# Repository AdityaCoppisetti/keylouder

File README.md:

hey im dhruv coppisetti and i love mechanical keyboards!
mainly 60 percents to be honest. 

with hackclub's macondo program where they fund you for the project that you make,
i decided that i should give this project a try and for the longest time i left it
abandoned because i couldn't figure out the keyboard layout, but then i watched a ton of
youtube tutorials and i got the hang of it. 

how is my keyboard different than other 60 percent keyboards?

well for starters its made completely by me including the pcb and the case and everything down to the tiniest bit

and then i did this really unique thing all because i had a tiny bit of space beneath the main controller of the keyboard (raspberry pi pico)
so i thought i should add a led matrix.

i was loooking at a tutorial where they had made their own led matrix module and it got me thinking what if i made my own
hotswappable modules

and so i did just that 

i made the keyboards pcb firstly and here is how that looks like 

but the wiring and the annotation was all wrong so i made it again plus i had totally forgotton to add stabilizers

so i made the schematic again and made a new pcb 

i landed with this pcb 

and the extra space beneath the pi pico gave me the idea and the space to add swappable modules 

and so i made a led matrix pcb and here is how that looks like 

the routing for this pcb took me A WHILLLEEE but i had  tons of fun doing it 
its really fun to take such tasks 

and the led matrix went onto the board so perfectly 

https://github.com/user-attachments/assets/e525fbdb-a991-4f65-9065-cdec64515798

and then i made 2 more modules 

the rotary encoder pcb which just changes the wiring 

i will be using that to adjust volume

and the most exciting part of the project is that i made a virtual pet inside the keyboard!

i made a tamagotchi module.

what a tamgotchi?

Tamagotchi is a brand of handheld digital pets created by Japanese toymaker Bandai, originally released in 1996.  The name is a portmanteau of the Japanese word tamago (egg) and watch, reflecting the device's egg-shaped design.

its a tiny digital pet 

i didnt have enough remaining pins on the pi pico so i made a esp32 devboard and then made it into a tiny module 

and then i wanted a skeleton case for the keyboard so i made this case on onshape 

although i might redesign the led matrix pcb again

im super duper excited to build this project when i get the funding for it. you can find all the resources i used in the journal.md in this repo

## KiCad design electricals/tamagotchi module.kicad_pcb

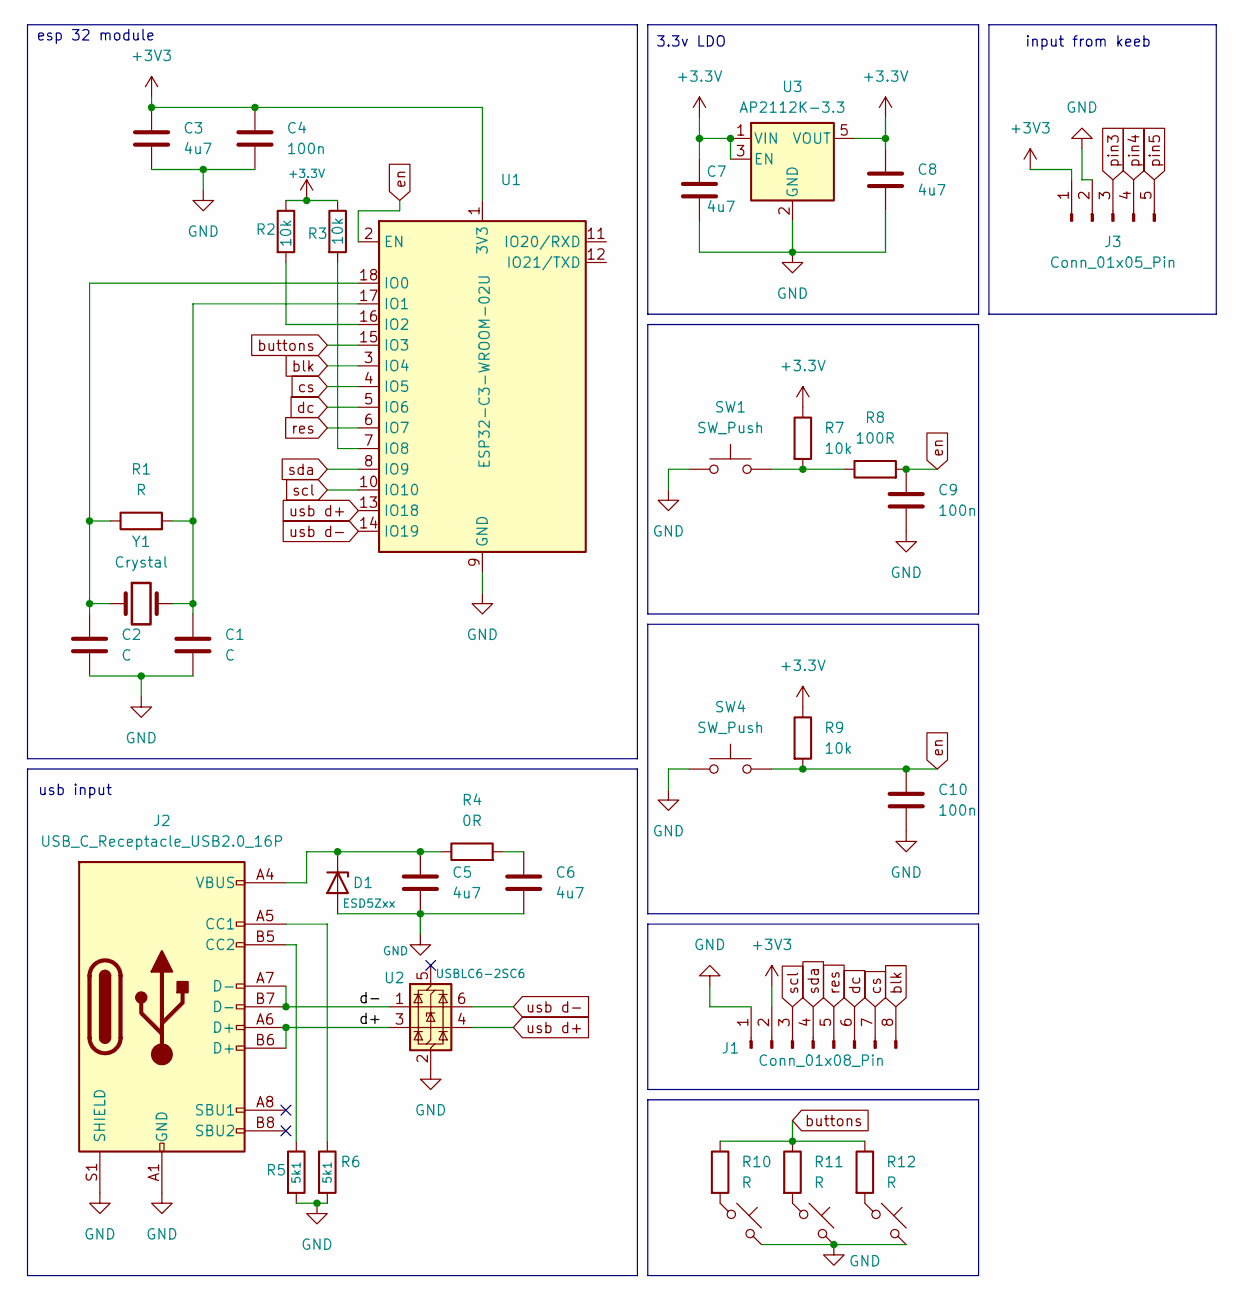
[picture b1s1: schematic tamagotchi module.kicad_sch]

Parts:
C1, C2: C; C_0201_0603Metric
C3, C5, C6, C7, C8: 4u7; C_0805_2012Metric
C4, C9, C10: 100n; C_0402_1005Metric
D1: ESD5Zxx; D_SOD-523
J1: Conn_01x08_Pin; PinHeader_1x08_P2.00mm_Vertical
J2: USB_C_Receptacle_USB2.0_16P; USB_C_Receptacle_G-Switch_GT-USB-7010ASV
J3: Conn_01x05_Pin; PinHeader_1x05_P2.00mm_Vertical
R1: R; R_0201_0603Metric
R2, R3, R7, R9: 10k; R_0402_1005Metric
R4: 0R; R_0805_2012Metric
R5, R6: 5k1; R_0402_1005Metric
R8: 100R; R_0402_1005Metric
R10, R11, R12: R; PinHeader_1x02_P2.00mm_Vertical
SW1, SW4: SW_Push; SW_SPST_B3U-1000P
SW2, SW3, SW6: SW_Push_45deg; SW_PUSH_6mm
U1: ESP32-C3-WROOM-02U
U2: USBLC6-2SC6; SOT-23-6
U3: AP2112K-3.3; SOT-23-5
Y1: Crystal; Crystal_SMD_3215-2Pin_3.2x1.5mm

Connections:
+3.3V: C7.1, C8.1, R2.1, R3.1, R7.1, R9.1, U3.1 (VIN), U3.3 (EN), U3.5 (VOUT)
+3V3: C3.1, C4.1, J1.2, J3.1, U1.1 (3V3)
/d+: J2.A6 (D+), J2.B6 (D+), U2.3 (I/O2)
/d-: J2.A7 (D-), J2.B7 (D-), U2.1 (I/O1)
GND: C1.2, C2.2, C3.2, C4.2, C5.2, C6.2, C7.2, C8.2, C9.2, C10.2, D1.2 (A), J1.1, J2.A1 (GND), J2.A12 (GND), J2.B1 (GND), J2.B12 (GND), J2.S1 (SHIELD), J3.2, R5.2, R6.2, SW1.1, SW2.2, SW3.2, SW4.1, SW6.2, U1.9 (GND), U1.19 (GND), U2.2 (GND), U3.2 (GND)
unnamed: C6.1, R4.2
unnamed: C5.1, D1.1 (K), J2.A4 (VBUS), J2.A9 (VBUS), J2.B4 (VBUS), J2.B9 (VBUS), R4.1
unnamed: J2.A5 (CC1), R6.1
unnamed: J2.B5 (CC2), R5.1
unnamed: R7.2, R8.1, SW1.2
unnamed: R10.2, SW3.1
unnamed: R11.2, SW2.1
unnamed: R12.2, SW6.1
unnamed: C2.1, R1.1, U1.18 (IO0), Y1.1
unnamed: C1.1, R1.2, U1.17 (IO1), Y1.2
unnamed: R2.2, U1.16 (IO2)
unnamed: R3.2, U1.7 (IO8)
blk: J1.8, U1.3 (IO4)
buttons: R10.1, R11.1, R12.1, U1.15 (IO3)
cs: J1.7, U1.4 (IO5)
dc: J1.6, U1.5 (IO6)
en: C9.1, C10.1, R8.2, R9.2, SW4.2, U1.2 (EN)
pin3: J3.3
pin4: J3.4
pin5: J3.5
res: J1.5, U1.6 (IO7)
scl: J1.3, U1.10 (IO10)
sda: J1.4, U1.8 (IO9)
usb d+: U1.13 (IO18), U2.4 (I/O2)
usb d-: U1.14 (IO19), U2.6 (I/O1)

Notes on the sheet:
3.3v LDO
usb input
esp 32 module
input from keeb

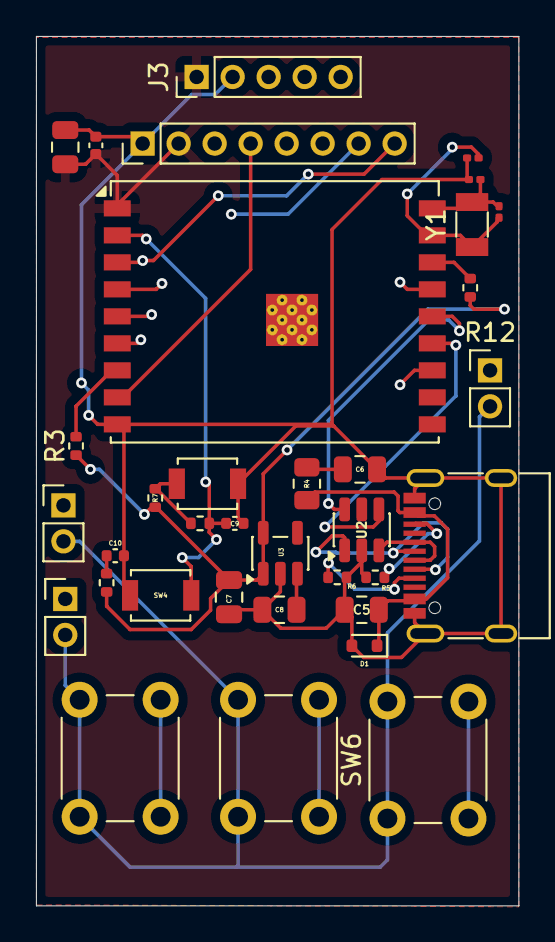
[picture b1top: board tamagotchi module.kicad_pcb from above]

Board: 4 copper layers, 26.8 x 48.3 mm, 35 parts (0 on the bottom side), 27 nets.

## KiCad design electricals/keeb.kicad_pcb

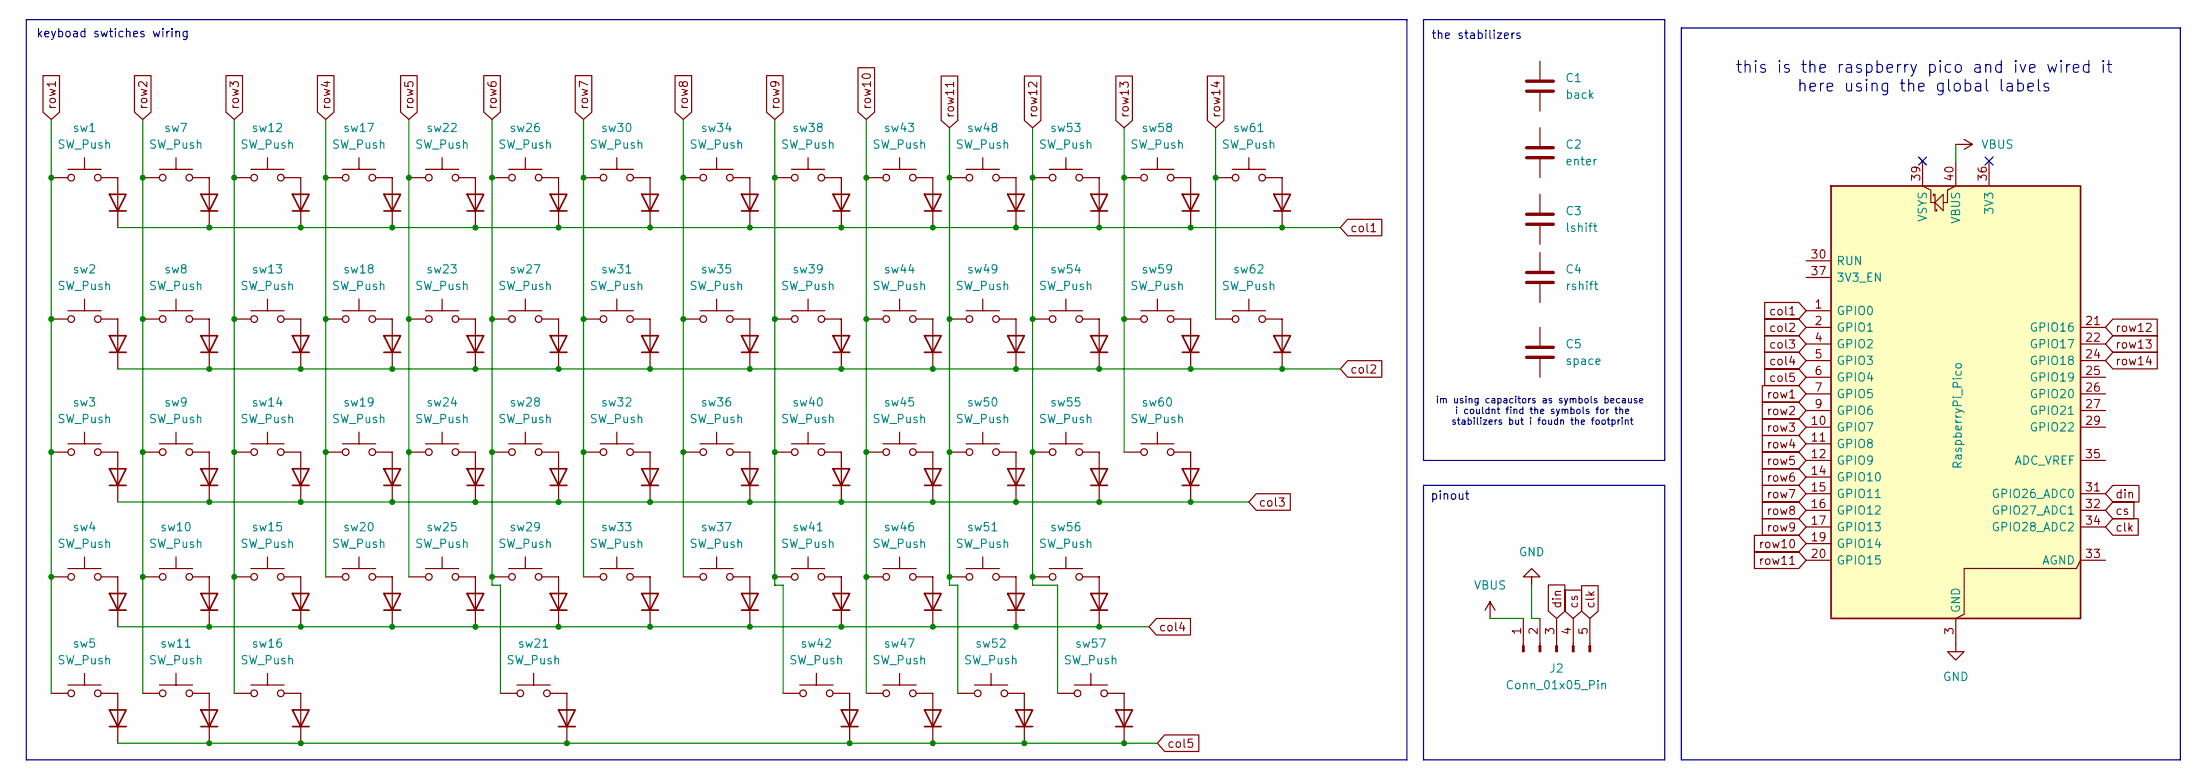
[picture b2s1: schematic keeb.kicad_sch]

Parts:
A1: RaspberryPi_Pico; RaspberryPi_Pico_Common_Unspecified
C1: back; Stabilizer_Cherry_MX_2.00u
C2: enter; Stabilizer_Cherry_MX_2.00u
C3: lshift; Stabilizer_Cherry_MX_2.00u
C4: rshift; Stabilizer_Cherry_MX_2.00u
C5: space; Stabilizer_Cherry_MX_6.25u
D1, D2, D3, D4, D5, D6, D7, D8, D9, D10, D11, D12, D13, D14, D15, D16, D17, D18, D19, D20, D21, D22, D23, D24, D25, D26, D27, D28, D29, D30, D31, D32, D33, D34, D35, D36, D37, D38, D39, D40, D41, D42, D43, D44, D45, D46, D47, D48, D49, D50, D51, D52, D53, D54, D55, D56, D57, D58, D59, D60, D61: 1N4148; D_DO-35_SOD27_P7.62mm_Horizontal
J2: Conn_01x05_Pin; PinHeader_1x05_P2.00mm_Vertical
sw1, sw7, sw8, sw9, sw10, sw12, sw13, sw14, sw15, sw17, sw18, sw19, sw20, sw22, sw23, sw24, sw25, sw26, sw27, sw28, sw29, sw30, sw31, sw32, sw33, sw34, sw35, sw36, sw37, sw38, sw39, sw40, sw41, sw43, sw44, sw45, sw46, sw48, sw49, sw50, sw51, sw53, sw54, sw55, sw58, sw59: SW_Push; SW_Cherry_MX_1.00u_PCB
sw2, sw62: SW_Push; SW_Cherry_MX_1.50u_PCB
sw3: SW_Push; SW_Cherry_MX_1.75u_PCB
sw4, sw60: SW_Push; SW_Cherry_MX_2.25u_PCB
sw5, sw11, sw16, sw42, sw47, sw52, sw57: SW_Push; SW_Cherry_MX_1.25u_PCB
sw21: SW_Push; SW_Cherry_MX_6.25u_PCB
sw56: SW_Push; SW_Cherry_MX_2.75u_PCB
sw61: SW_Push; SW_Cherry_MX_2.00u_PCB

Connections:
GND: A1.3 (GND), A1.8 (GND), A1.13 (GND), A1.18 (GND), A1.23 (GND), A1.28 (GND), A1.38 (GND), J2.2
unnamed: D1.2 (A), sw1.2
unnamed: D2.2 (A), sw2.2
unnamed: D3.2 (A), sw3.2
unnamed: D4.2 (A), sw4.2
unnamed: D5.2 (A), sw5.2
unnamed: D6.2 (A), sw7.2
unnamed: D7.2 (A), sw8.2
unnamed: D8.2 (A), sw9.2
unnamed: D9.2 (A), sw10.2
unnamed: D10.2 (A), sw11.2
unnamed: D11.2 (A), sw12.2
unnamed: D12.2 (A), sw13.2
unnamed: D13.2 (A), sw14.2
unnamed: D14.2 (A), sw15.2
unnamed: D15.2 (A), sw16.2
unnamed: D16.2 (A), sw17.2
unnamed: D17.2 (A), sw18.2
unnamed: D18.2 (A), sw19.2
unnamed: D19.2 (A), sw20.2
unnamed: D20.2 (A), sw21.2
unnamed: D21.2 (A), sw22.2
unnamed: D22.2 (A), sw23.2
unnamed: D23.2 (A), sw24.2
unnamed: D24.2 (A), sw25.2
unnamed: D25.2 (A), sw26.2
unnamed: D26.2 (A), sw27.2
unnamed: D27.2 (A), sw28.2
unnamed: D28.2 (A), sw29.2
unnamed: D29.2 (A), sw30.2
unnamed: D30.2 (A), sw31.2
unnamed: D31.2 (A), sw32.2
unnamed: D32.2 (A), sw33.2
unnamed: D33.2 (A), sw34.2
unnamed: D34.2 (A), sw35.2
unnamed: D35.2 (A), sw36.2
unnamed: D36.2 (A), sw37.2
unnamed: D37.2 (A), sw38.2
unnamed: D38.2 (A), sw39.2
unnamed: D39.2 (A), sw40.2
unnamed: D40.2 (A), sw41.2
unnamed: D41.2 (A), sw42.2
unnamed: D42.2 (A), sw43.2
unnamed: D43.2 (A), sw44.2
unnamed: D44.2 (A), sw45.2
unnamed: D45.2 (A), sw46.2
unnamed: D46.2 (A), sw47.2
unnamed: D47.2 (A), sw48.2
unnamed: D48.2 (A), sw49.2
unnamed: D49.2 (A), sw50.2
unnamed: D50.2 (A), sw51.2
unnamed: D51.2 (A), sw52.2
unnamed: D52.2 (A), sw53.2
unnamed: D53.2 (A), sw54.2
unnamed: D54.2 (A), sw55.2
unnamed: D55.2 (A), sw56.2
unnamed: D56.2 (A), sw57.2
unnamed: D57.2 (A), sw58.2
unnamed: D58.2 (A), sw59.2
unnamed: D59.2 (A), sw60.2
unnamed: D60.2 (A), sw61.2
unnamed: D61.2 (A), sw62.2
VBUS: A1.40 (VBUS), J2.1
clk: A1.34 (GPIO28_ADC2), J2.5
col1: A1.1 (GPIO0), D1.1 (K), D6.1 (K), D11.1 (K), D16.1 (K), D21.1 (K), D25.1 (K), D29.1 (K), D33.1 (K), D37.1 (K), D42.1 (K), D47.1 (K), D52.1 (K), D57.1 (K), D60.1 (K)
col2: A1.2 (GPIO1), D2.1 (K), D7.1 (K), D12.1 (K), D17.1 (K), D22.1 (K), D26.1 (K), D30.1 (K), D34.1 (K), D38.1 (K), D43.1 (K), D48.1 (K), D53.1 (K), D58.1 (K), D61.1 (K)
col3: A1.4 (GPIO2), D3.1 (K), D8.1 (K), D13.1 (K), D18.1 (K), D23.1 (K), D27.1 (K), D31.1 (K), D35.1 (K), D39.1 (K), D44.1 (K), D49.1 (K), D54.1 (K), D59.1 (K)
col4: A1.5 (GPIO3), D4.1 (K), D9.1 (K), D14.1 (K), D19.1 (K), D24.1 (K), D28.1 (K), D32.1 (K), D36.1 (K), D40.1 (K), D45.1 (K), D50.1 (K), D55.1 (K)
col5: A1.6 (GPIO4), D5.1 (K), D10.1 (K), D15.1 (K), D20.1 (K), D41.1 (K), D46.1 (K), D51.1 (K), D56.1 (K)
cs: A1.32 (GPIO27_ADC1), J2.4
din: A1.31 (GPIO26_ADC0), J2.3
row1: A1.7 (GPIO5), sw1.1, sw2.1, sw3.1, sw4.1, sw5.1
row2: A1.9 (GPIO6), sw7.1, sw8.1, sw9.1, sw10.1, sw11.1
row3: A1.10 (GPIO7), sw12.1, sw13.1, sw14.1, sw15.1, sw16.1
row4: A1.11 (GPIO8), sw17.1, sw18.1, sw19.1, sw20.1
row5: A1.12 (GPIO9), sw22.1, sw23.1, sw24.1, sw25.1
row6: A1.14 (GPIO10), sw21.1, sw26.1, sw27.1, sw28.1, sw29.1
row7: A1.15 (GPIO11), sw30.1, sw31.1, sw32.1, sw33.1
row8: A1.16 (GPIO12), sw34.1, sw35.1, sw36.1, sw37.1
row9: A1.17 (GPIO13), sw38.1, sw39.1, sw40.1, sw41.1, sw42.1
row10: A1.19 (GPIO14), sw43.1, sw44.1, sw45.1, sw46.1, sw47.1
row11: A1.20 (GPIO15), sw48.1, sw49.1, sw50.1, sw51.1, sw52.1
row12: A1.21 (GPIO16), sw53.1, sw54.1, sw55.1, sw56.1, sw57.1
row13: A1.22 (GPIO17), sw58.1, sw59.1, sw60.1
row14: A1.24 (GPIO18), sw61.1, sw62.1

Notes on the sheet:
the stabilizers
pinout
this is the raspberry pico and ive wired it here using the global labels
keyboad swtiches wiring
im using capacitors as symbols because i couldnt find the symbols for the stabilizers but i foudn the footprint

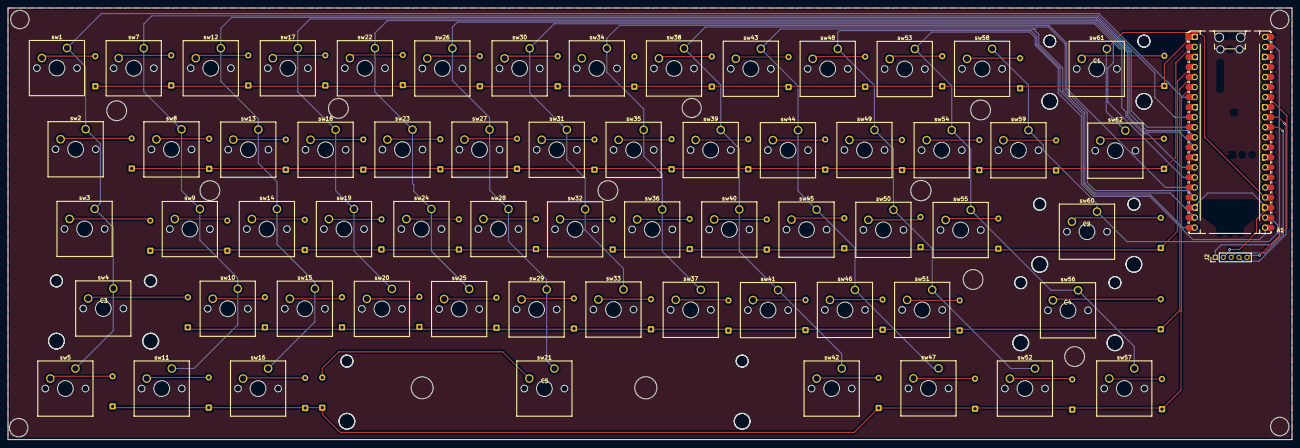
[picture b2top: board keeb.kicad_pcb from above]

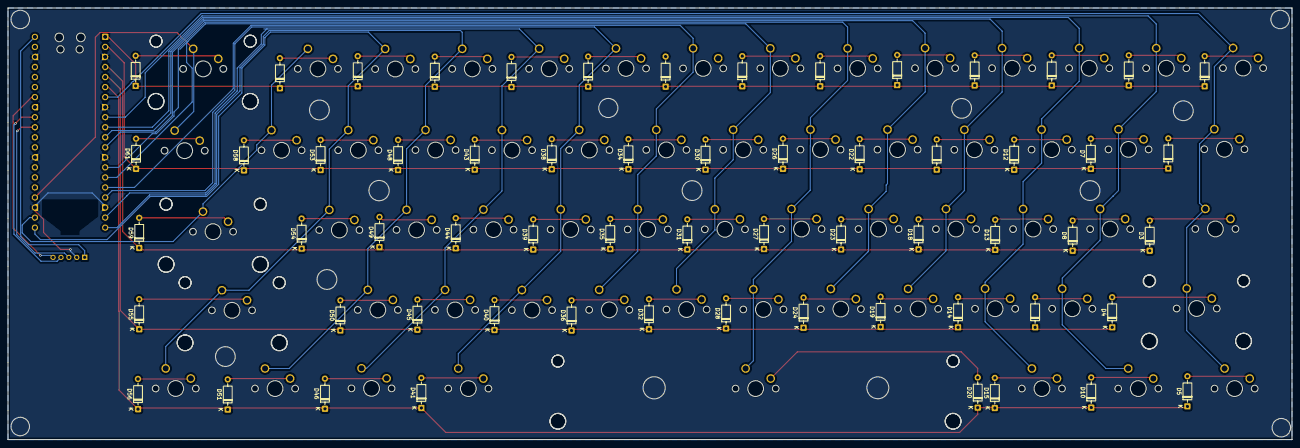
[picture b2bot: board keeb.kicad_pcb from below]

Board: 2 copper layers, 324.9 x 109.2 mm, 129 parts (61 on the bottom side), 85 nets.

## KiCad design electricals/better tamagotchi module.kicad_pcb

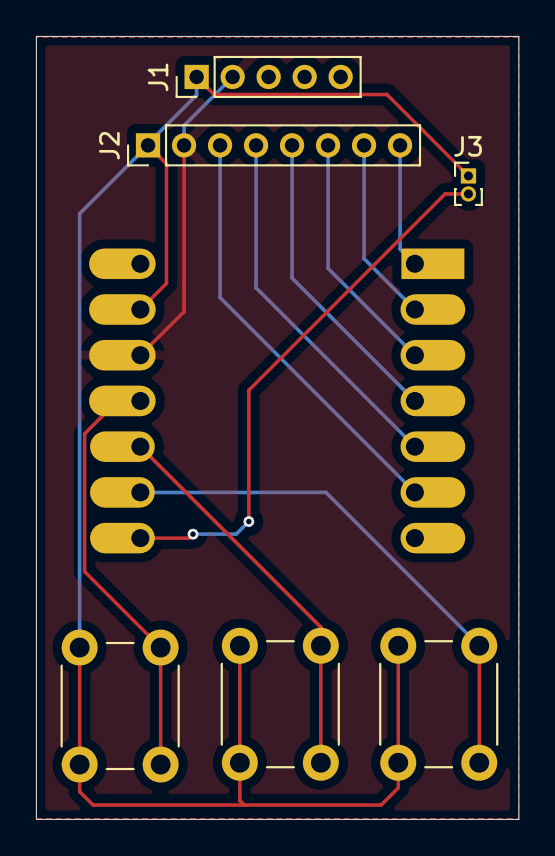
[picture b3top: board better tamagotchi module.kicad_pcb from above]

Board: 2 copper layers, 26.8 x 43.5 mm, 7 parts (1 on the bottom side), 12 nets.

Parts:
J1: Conn_01x05_Pin; PinHeader_1x05_P2.00mm_Vertical
J2: Conn_01x08_Pin; PinHeader_1x08_P2.00mm_Vertical
J3: Conn_01x02_Pin; PinHeader_1x02_P1.00mm_Vertical
SW1, SW2, SW3: SW_Push; SW_PUSH_6mm
U1: MOUDLE-SEEEDUINO-XIAO; XIAO-Generic-Hybrid-14P-2.54-21X17.8MM

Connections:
+3V3: J1.2, J2.2, U1.12 (3V3)
GND: J1.1, J2.1, J3.1, SW1.1, SW2.1, SW3.1, U1.13 (GND)
bkl: J2.8, U1.1 (PA02_A0_D0)
buzz: J3.2, U1.8 (PB09_A7_D7_RX)
cs: J2.7, U1.2 (PA4_A1_D1)
dc: J2.6, U1.3 (PA10_A2_D2)
res: J2.5, U1.4 (PA11_A3_D3)
scl: J2.3, U1.6 (PA9_A5_D5_SCL)
sda: J2.4, U1.5 (PA8_A4_D4_SDA)
sw1: SW1.2, U1.11 (PA6_A10_D10_MOSI)
sw2: SW2.2, U1.10 (PA5_A9_D9_MISO)
sw3: SW3.2, U1.9 (PA7_A8_D8_SCK)

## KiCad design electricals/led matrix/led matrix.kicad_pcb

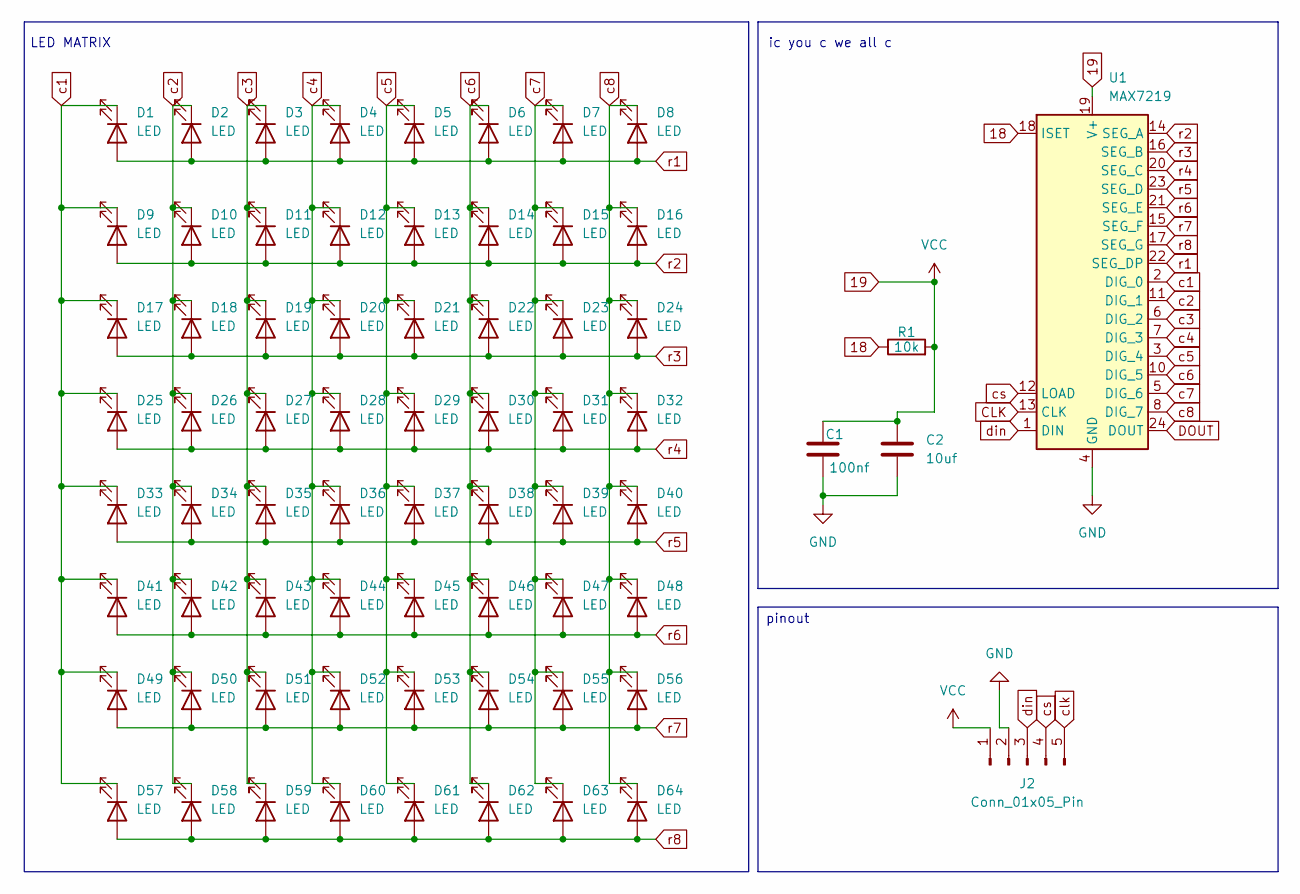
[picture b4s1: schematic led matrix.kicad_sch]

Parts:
C1: 100nf; C_0603_1608Metric
C2: 10uf; C_0805_2012Metric
D1, D2, D3, D4, D5, D6, D7, D8, D9, D10, D11, D12, D13, D14, D15, D16, D17, D18, D19, D20, D21, D22, D23, D24, D25, D26, D27, D28, D29, D30, D31, D32, D33, D34, D35, D36, D37, D38, D39, D40, D41, D42, D43, D44, D45, D46, D47, D48, D49, D50, D51, D52, D53, D54, D55, D56, D57, D58, D59, D60, D61, D62, D63, D64: LED; LED_0201_0603Metric
J2: Conn_01x05_Pin; PinHeader_1x05_P2.00mm_Vertical
R1: 10k; R_0603_1608Metric
U1: MAX7219; SOIC-24W_7.5x15.4mm_P1.27mm

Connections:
18: R1.1, U1.18 (ISET)
19: C1.1, C2.1, J2.1, R1.2, U1.19 (V+)
DOUT: U1.24 (DOUT)
GND: C1.2, C2.2, J2.2, U1.4 (GND), U1.9 (GND)
c1: D1.1 (K), D9.1 (K), D17.1 (K), D25.1 (K), D33.1 (K), D41.1 (K), D49.1 (K), D57.1 (K), U1.2 (DIG_0)
c2: D2.1 (K), D10.1 (K), D18.1 (K), D26.1 (K), D34.1 (K), D42.1 (K), D50.1 (K), D58.1 (K), U1.11 (DIG_1)
c3: D3.1 (K), D11.1 (K), D19.1 (K), D27.1 (K), D35.1 (K), D43.1 (K), D51.1 (K), D59.1 (K), U1.6 (DIG_2)
c4: D4.1 (K), D12.1 (K), D20.1 (K), D28.1 (K), D36.1 (K), D44.1 (K), D52.1 (K), D60.1 (K), U1.7 (DIG_3)
c5: D5.1 (K), D13.1 (K), D21.1 (K), D29.1 (K), D37.1 (K), D45.1 (K), D53.1 (K), D61.1 (K), U1.3 (DIG_4)
c6: D6.1 (K), D14.1 (K), D22.1 (K), D30.1 (K), D38.1 (K), D46.1 (K), D54.1 (K), D62.1 (K), U1.10 (DIG_5)
c7: D7.1 (K), D15.1 (K), D23.1 (K), D31.1 (K), D39.1 (K), D47.1 (K), D55.1 (K), D63.1 (K), U1.5 (DIG_6)
c8: D8.1 (K), D16.1 (K), D24.1 (K), D32.1 (K), D40.1 (K), D48.1 (K), D56.1 (K), D64.1 (K), U1.8 (DIG_7)
clk: J2.5, U1.13 (CLK)
cs: J2.4, U1.12 (LOAD)
din: J2.3, U1.1 (DIN)
r1: D1.2 (A), D2.2 (A), D3.2 (A), D4.2 (A), D5.2 (A), D6.2 (A), D7.2 (A), D8.2 (A), U1.22 (SEG_DP)
r2: D9.2 (A), D10.2 (A), D11.2 (A), D12.2 (A), D13.2 (A), D14.2 (A), D15.2 (A), D16.2 (A), U1.14 (SEG_A)
r3: D17.2 (A), D18.2 (A), D19.2 (A), D20.2 (A), D21.2 (A), D22.2 (A), D23.2 (A), D24.2 (A), U1.16 (SEG_B)
r4: D25.2 (A), D26.2 (A), D27.2 (A), D28.2 (A), D29.2 (A), D30.2 (A), D31.2 (A), D32.2 (A), U1.20 (SEG_C)
r5: D33.2 (A), D34.2 (A), D35.2 (A), D36.2 (A), D37.2 (A), D38.2 (A), D39.2 (A), D40.2 (A), U1.23 (SEG_D)
r6: D41.2 (A), D42.2 (A), D43.2 (A), D44.2 (A), D45.2 (A), D46.2 (A), D47.2 (A), D48.2 (A), U1.21 (SEG_E)
r7: D49.2 (A), D50.2 (A), D51.2 (A), D52.2 (A), D53.2 (A), D54.2 (A), D55.2 (A), D56.2 (A), U1.15 (SEG_F)
r8: D57.2 (A), D58.2 (A), D59.2 (A), D60.2 (A), D61.2 (A), D62.2 (A), D63.2 (A), D64.2 (A), U1.17 (SEG_G)

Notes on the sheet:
pinout
ic you c we all c
LED MATRIX

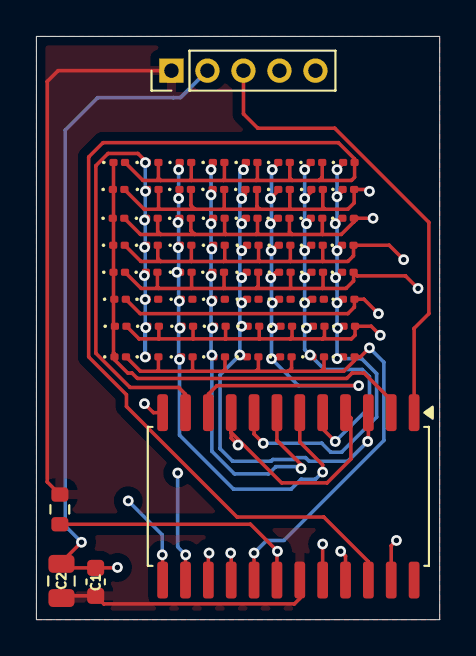
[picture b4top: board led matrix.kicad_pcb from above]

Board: 4 copper layers, 22.4 x 32.4 mm, 69 parts (0 on the bottom side), 22 nets.

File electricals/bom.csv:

Module,Component,Quantity,Price (INR),Link,Price (USD)
Keyboard,Raspberry Pi Pico,1,1060,https://amzn.in/d/02R50tLO,$11.08
Keyboard,1N4148 DO-35 switching diode,61,294,https://robu.in/product/1n4148-onsemi-100v-1v10ma-4ns-200ma-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,$3.07
Keyboard,Womier Retro Ruby Pink Cherry Doubleshot PBT Keycaps,1,1899,https://curiositycaps.in/products/womier-retro-ruby-pink-che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,$19.84
Keyboard,Blue mechanical switches,90,2187,https://amzn.in/d/03xjlYV7,$22.85
Keyboard,Keyboard stabilizers,1,1716,https://amzn.in/d/0fbE7VLn,$17.93
Keyboard,2.00mm pitch female Berg strip,1,25,https://robu.in/product/2mm-pitch-female-berg-strip-40x1-2pcs/,$0.26
Keyboard,Keyboard PCB,1,900,robu.in,$9.40
Rotary Encoder,Rotary encoder module,1,92,https://robu.in/product/m274-360-degree-rotary-encoder-modul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,$0.96
Rotary Encoder,Perfboard,1,75,https://amzn.in/d/09jRTxoF,$0.78
Rotary Encoder,360-degree rotary encoder module,1,92,https://robu.in/product/m274-360-degree-rotary-encoder-modul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,$0.96
LED Matrix,100nF / 0.1uF 0603 SMD ceramic capacitor,1,4.4,https://robu.in/product/0603b104k101nt-fh-100v-100nf-x7r%c2%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,$0.05
LED Matrix,10uF 0603 SMD ceramic capacitor,1,39,https://robu.in/product/zrb18ar61e106me01l-murata-smd-multil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,$0.41
LED Matrix,0603 SMD red LED,64,133,https://robu.in/product/19-217-r6c-al1m2vy-3t-everlight-red-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,$1.39
LED Matrix,10k 0603 SMD resistor,1,4.8,https://robu.in/product/yageo-10k-ohm-1-4w-0603-surface-moun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,$0.05
LED Matrix,MAX7219 SMD IC,1,128,https://robu.in/product/max7219-ic-smd-package-8-digit-led-d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,$1.34
LED Matrix,PCB,1,900,https://robu.in/,$9.40
Tamagotchi,GC9A01 1.28-inch 240x240 round display,1,519,https://robu.in/product/goldenmorning-gc9a01-7p-240x240-spi-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,$5.42
Tamagotchi,6x6mm through-hole tactile switch,1,7,https://robu.in/product/tsd001a06026a-bzcn-6mm-6mm-50ma-roun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,$0.07
Tamagotchi,PCB,1,900,https://robu.in/,$9.40
,,,,,
,,,,,
,,,,total amount is 115 dollars,

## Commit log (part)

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2026-06-10 Add files via upload
    this is the work louder keyboard that ill be using as reference
